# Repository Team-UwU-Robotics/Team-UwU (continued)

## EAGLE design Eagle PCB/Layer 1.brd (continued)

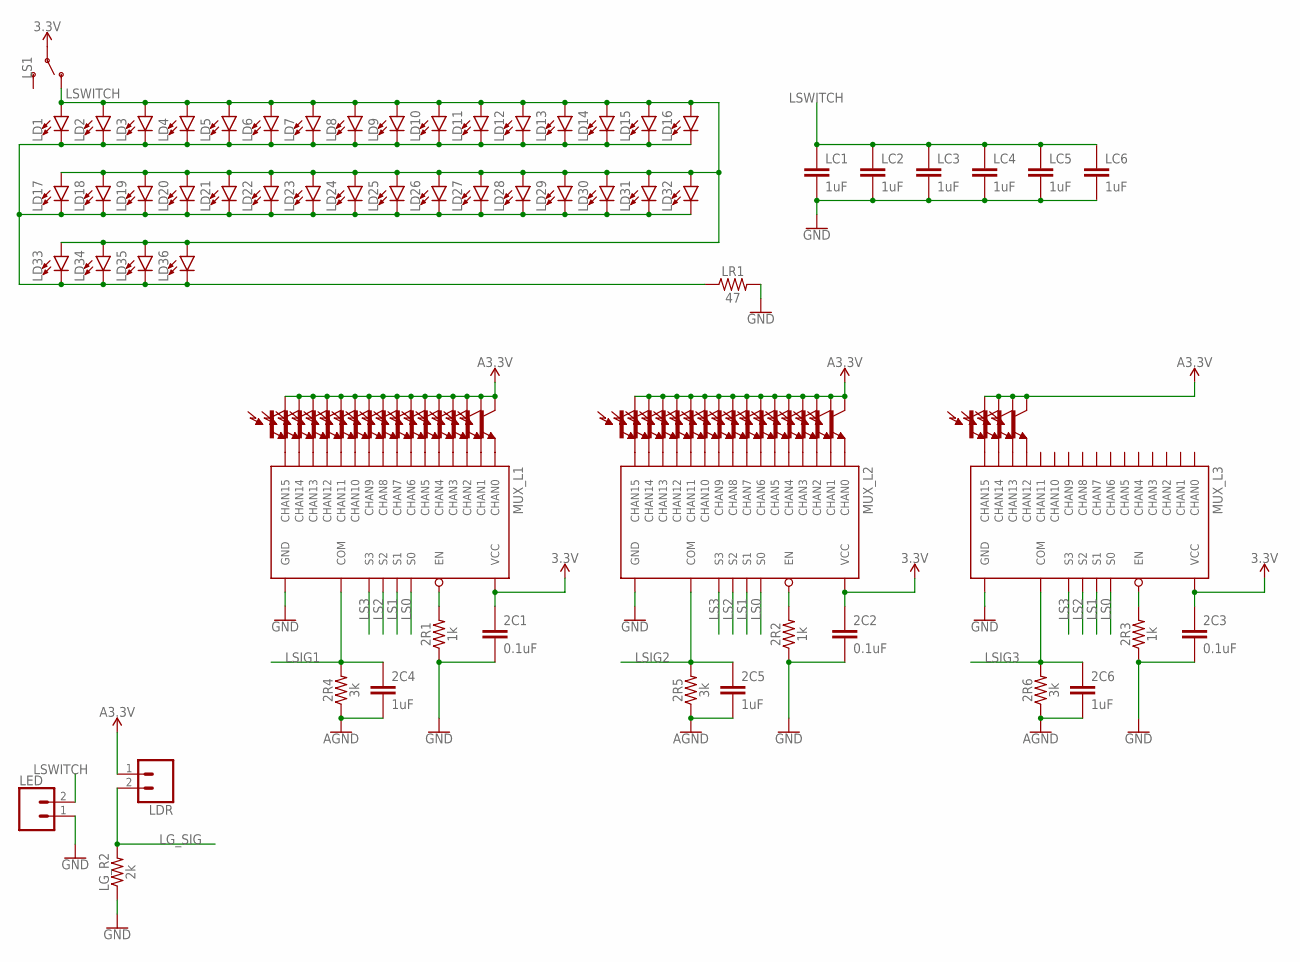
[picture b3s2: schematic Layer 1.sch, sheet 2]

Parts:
2C1, 2C2, 2C3: 0.1uF; C0603
2C4, 2C5, 2C6: 1uF; C0603
2R1, 2R2, 2R3: 1k; R0603
2R4, 2R5, 2R6: 3k; R0603
LC1, LC2, LC3, LC4, LC5, LC6: 1uF; C0603
LD1, LD2, LD3, LD4, LD5, LD6, LD7, LD8, LD9, LD10, LD11, LD12, LD13, LD14, LD15, LD16, LD17, LD18, LD19, LD20, LD21, LD22, LD23, LD24, LD25, LD26, LD27, LD28, LD29, LD30, LD31, LD32, LD33, LD34, LD35, LD36: 3528LED; 3528
LDR: CONN_021X02_NO_SILK; 1X02_NO_SILK
LED: CONN_02POLAR; MOLEX-1X2
LG_R2: 2k; R0603
LR1: 47; R0603
LS1: SWITCH-SPDT-PTH-11.6X4.0MM-LOCK; SWITCH_SPDT_PTH_11.6X4.0MM_LOCK
MUX_L1, MUX_L2, MUX_L3: 74HC4067SSOP-24; SSOP24
Q1, Q2, Q3, Q4, Q5, Q6, Q7, Q8, Q9, Q10, Q11, Q12, Q13, Q14, Q15, Q16, Q17, Q18, Q19, Q20, Q21, Q22, Q23, Q24, Q25, Q26, Q27, Q28, Q29, Q30, Q31, Q32, Q33, Q34, Q35, Q36: LIGHT_SENSORALS; ALS-PT19

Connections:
3.3V: 2C1.1, 2C2.1, 2C3.1, LS1.2, MUX_L1.24 (VCC), MUX_L2.24 (VCC), MUX_L3.24 (VCC); also elsewhere on the board
AGND: 2C4.2, 2C5.2, 2C6.2, 2R4.1, 2R5.1, 2R6.1; also elsewhere on the board
GND: 2C1.2, 2C2.2, 2C3.2, 2R1.1, 2R2.1, 2R3.1, LC1.2, LC2.2, LC3.2, LC4.2, LC5.2, LC6.2, LED.1, LG_R2.1, LR1.2, MUX_L1.12 (GND), MUX_L2.12 (GND), MUX_L3.12 (GND); also elsewhere on the board
LG_SIG: LDR.2, LG_R2.2; also elsewhere on the board
LS0: MUX_L1.10 (S0), MUX_L2.10 (S0), MUX_L3.10 (S0); also elsewhere on the board
LS1: MUX_L1.11 (S1), MUX_L2.11 (S1), MUX_L3.11 (S1); also elsewhere on the board
LS2: MUX_L1.14 (S2), MUX_L2.14 (S2), MUX_L3.14 (S2); also elsewhere on the board
LS3: MUX_L1.13 (S3), MUX_L2.13 (S3), MUX_L3.13 (S3); also elsewhere on the board
LSIG1: 2C4.1, 2R4.2, MUX_L1.1 (COM); also elsewhere on the board
LSIG2: 2C5.1, 2R5.2, MUX_L2.1 (COM); also elsewhere on the board
LSIG3: 2C6.1, 2R6.2, MUX_L3.1 (COM); also elsewhere on the board
LSWITCH: LC1.1, LC2.1, LC3.1, LC4.1, LC5.1, LC6.1, LD1.A, LD2.A, LD3.A, LD4.A, LD5.A, LD6.A, LD7.A, LD8.A, LD9.A, LD10.A, LD11.A, LD12.A, LD13.A, LD14.A, LD15.A, LD16.A, LD17.A, LD18.A, LD19.A, LD20.A, LD21.A, LD22.A, LD23.A, LD24.A, LD25.A, LD26.A, LD27.A, LD28.A, LD29.A, LD30.A, LD31.A, LD32.A, LD33.A, LD34.A, LD35.A, LD36.A, LED.2, LS1.1 (O)
unnamed: 2R1.2, MUX_L1.15 (EN)
unnamed: MUX_L1.16 (CHAN15), Q1.E (E1)
unnamed: MUX_L1.17 (CHAN14), Q2.E (E1)
unnamed: MUX_L1.18 (CHAN13), Q3.E (E1)
unnamed: MUX_L1.19 (CHAN12), Q4.E (E1)
unnamed: MUX_L1.20 (CHAN11), Q5.E (E1)
unnamed: MUX_L1.21 (CHAN10), Q6.E (E1)
unnamed: MUX_L1.22 (CHAN9), Q7.E (E1)
unnamed: MUX_L1.23 (CHAN8), Q8.E (E1)
unnamed: MUX_L1.2 (CHAN7), Q9.E (E1)
unnamed: MUX_L1.3 (CHAN6), Q10.E (E1)
unnamed: MUX_L1.4 (CHAN5), Q11.E (E1)
unnamed: MUX_L1.5 (CHAN4), Q12.E (E1)
unnamed: MUX_L1.6 (CHAN3), Q13.E (E1)
unnamed: MUX_L1.7 (CHAN2), Q14.E (E1)
unnamed: MUX_L1.8 (CHAN1), Q15.E (E1)
unnamed: MUX_L1.9 (CHAN0), Q16.E (E1)
unnamed: LD1.C, LD2.C, LD3.C, LD4.C, LD5.C, LD6.C, LD7.C, LD8.C, LD9.C, LD10.C, LD11.C, LD12.C, LD13.C, LD14.C, LD15.C, LD16.C, LD17.C, LD18.C, LD19.C, LD20.C, LD21.C, LD22.C, LD23.C, LD24.C, LD25.C, LD26.C, LD27.C, LD28.C, LD29.C, LD30.C, LD31.C, LD32.C, LD33.C, LD34.C, LD35.C, LD36.C, LR1.1
unnamed: 2R2.2, MUX_L2.15 (EN)
unnamed: MUX_L2.16 (CHAN15), Q17.E (E1)
unnamed: MUX_L2.17 (CHAN14), Q18.E (E1)
unnamed: MUX_L2.18 (CHAN13), Q19.E (E1)
unnamed: MUX_L2.19 (CHAN12), Q20.E (E1)
unnamed: MUX_L2.20 (CHAN11), Q21.E (E1)
unnamed: MUX_L2.21 (CHAN10), Q22.E (E1)
unnamed: MUX_L2.22 (CHAN9), Q23.E (E1)
unnamed: MUX_L2.23 (CHAN8), Q24.E (E1)
unnamed: MUX_L2.2 (CHAN7), Q25.E (E1)
unnamed: MUX_L2.3 (CHAN6), Q26.E (E1)
unnamed: MUX_L2.4 (CHAN5), Q27.E (E1)
unnamed: MUX_L2.5 (CHAN4), Q28.E (E1)
unnamed: MUX_L2.6 (CHAN3), Q29.E (E1)
unnamed: MUX_L2.7 (CHAN2), Q30.E (E1)
unnamed: MUX_L2.8 (CHAN1), Q31.E (E1)
unnamed: MUX_L2.9 (CHAN0), Q32.E (E1)
unnamed: 2R3.2, MUX_L3.15 (EN)
unnamed: MUX_L3.16 (CHAN15), Q33.E (E1)
unnamed: MUX_L3.17 (CHAN14), Q34.E (E1)
unnamed: MUX_L3.18 (CHAN13), Q35.E (E1)
unnamed: MUX_L3.19 (CHAN12), Q36.E (E1)
VCCA: LDR.1, Q1.C (C1), Q2.C (C1), Q3.C (C1), Q4.C (C1), Q5.C (C1), Q6.C (C1), Q7.C (C1), Q8.C (C1), Q9.C (C1), Q10.C (C1), Q11.C (C1), Q12.C (C1), Q13.C (C1), Q14.C (C1), Q15.C (C1), Q16.C (C1), Q17.C (C1), Q18.C (C1), Q19.C (C1), Q20.C (C1), Q21.C (C1), Q22.C (C1), Q23.C (C1), Q24.C (C1), Q25.C (C1), Q26.C (C1), Q27.C (C1), Q28.C (C1), Q29.C (C1), Q30.C (C1), Q31.C (C1), Q32.C (C1), Q33.C (C1), Q34.C (C1), Q35.C (C1), Q36.C (C1); also elsewhere on the board

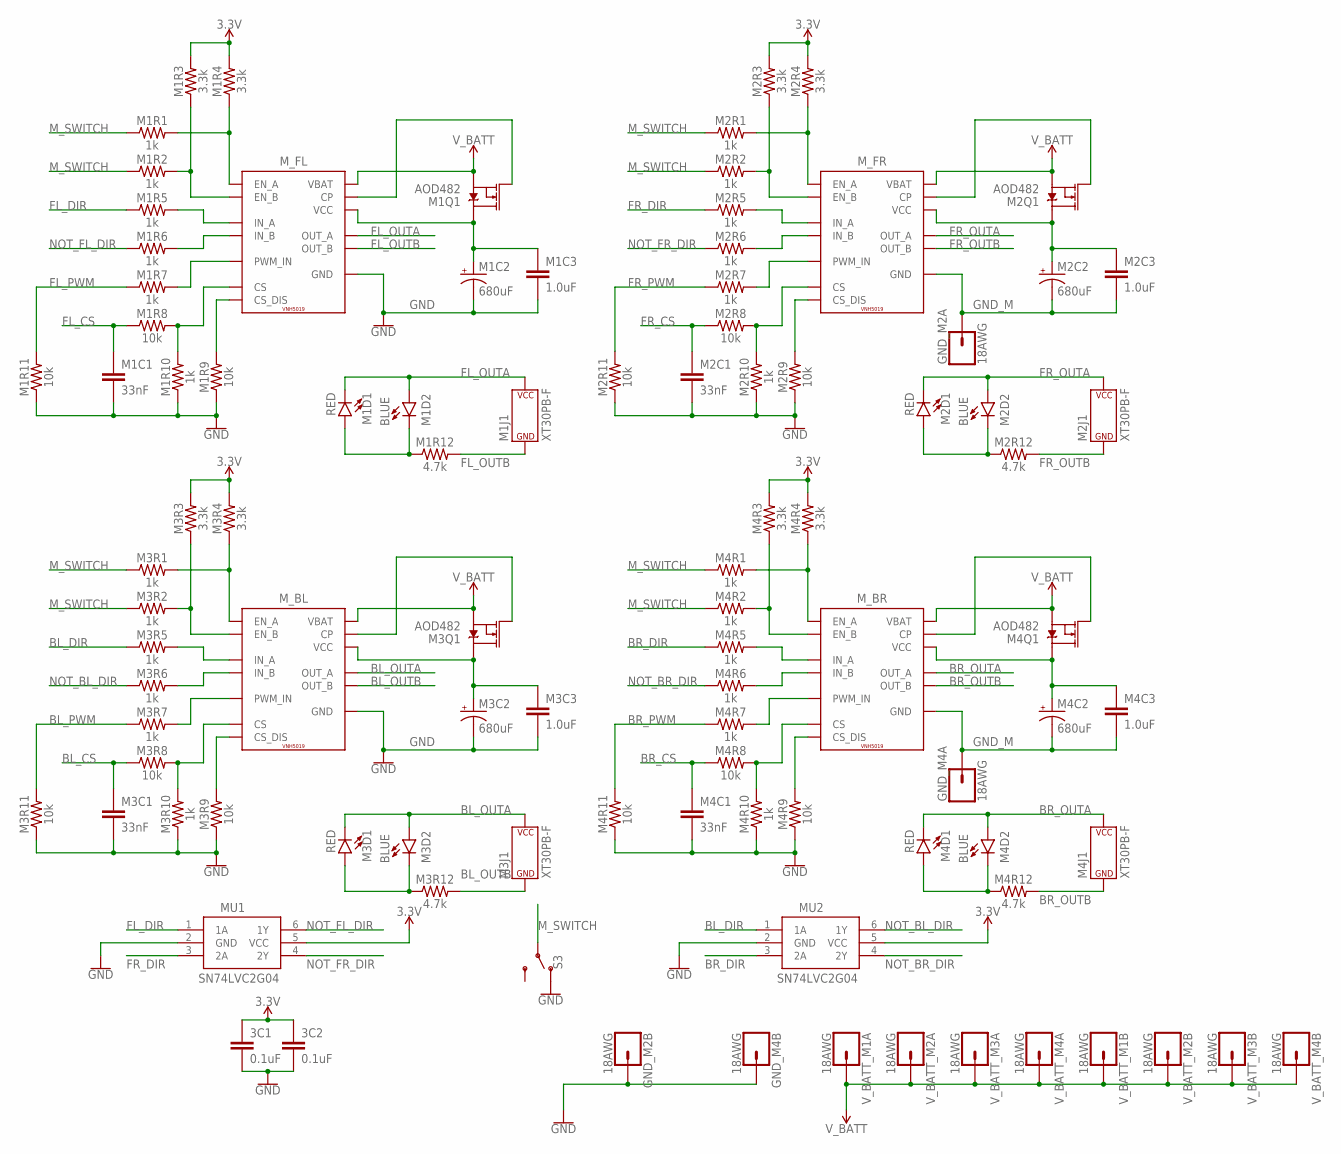
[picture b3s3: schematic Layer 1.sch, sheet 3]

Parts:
3C1, 3C2: 0.1uF; C0603
GND_M2A, GND_M2B, GND_M4A, GND_M4B: 18AWG
M1C1, M2C1, M3C1, M4C1: 33nF; C0603
M1C2, M2C2, M3C2, M4C2: 680uF; 3.5MM_CAP
M1C3, M2C3, M3C3, M4C3: 1.0uF; C0603
M1D1, M2D1, M3D1, M4D1: RED; LED-0603
M1D2, M2D2, M3D2, M4D2: BLUE; LED-0603
M1J1, M2J1, M3J1, M4J1: XT30PB-F
M1Q1, M2Q1, M3Q1, M4Q1: AOD482; DPAK
M1R1, M1R2, M1R5, M1R6, M1R7, M1R10, M2R1, M2R2, M2R5, M2R6, M2R7, M2R10, M3R1, M3R2, M3R5, M3R6, M3R7, M3R10, M4R1, M4R2, M4R5, M4R6, M4R7, M4R10: 1k; R0603
M1R3, M1R4, M2R3, M2R4, M3R3, M3R4, M4R3, M4R4: 3.3k; R0603
M1R8, M1R9, M1R11, M2R8, M2R9, M2R11, M3R8, M3R9, M3R11, M4R8, M4R9, M4R11: 10k; R0603
M1R12, M2R12, M3R12, M4R12: 4.7k; R0603
MU1, MU2: SN74LVC2G04DBVR; SOT23-6
M_BL: VNH5019; POWERSO-30
M_BR: VNH5019; POWERSO-30
M_FL: VNH5019; POWERSO-30
M_FR: VNH5019; POWERSO-30
S3: SWITCH-SPDT-PTH-11.6X4.0MM-LOCK; SWITCH_SPDT_PTH_11.6X4.0MM_LOCK
V_BATT_M1A, V_BATT_M1B, V_BATT_M2A, V_BATT_M2B, V_BATT_M3A, V_BATT_M3B, V_BATT_M4A, V_BATT_M4B: 18AWG

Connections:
3.3V: 3C1.1, 3C2.1, M1R3.2, M1R4.2, M2R3.2, M2R4.2, M3R3.2, M3R4.2, M4R3.2, M4R4.2, MU1.5 (VCC), MU2.5 (VCC); also elsewhere on the board
BL_CS: M3C1.1, M3R8.1; also elsewhere on the board
BL_DIR: M3R5.1, MU2.1 (1A); also elsewhere on the board
BL_OUTA: M3D1.C, M3D2.A, M3J1.+ (P$V+), M_BL.P1 (OUT_A), M_BL.P25 (OUT_A), M_BL.P30 (OUT_A), M_BL.P$1 (OUT_A), M_BL.P$2 (OUT_A), M_BL.P$3 (OUT_A), M_BL.P$4 (OUT_A), M_BL.P$5 (OUT_A), M_BL.P$6 (OUT_A), M_BL.P$7 (OUT_A), M_BL.P$8 (OUT_A), M_BL.P$9 (OUT_A), M_BL.SLUG2 (OUT_A)
BL_OUTB: M3J1.- (P$V-), M3R12.2, M_BL.P15 (OUT_B), M_BL.P16 (OUT_B), M_BL.P21 (OUT_B), M_BL.P$10 (OUT_B), M_BL.P$11 (OUT_B), M_BL.P$12 (OUT_B), M_BL.P$13 (OUT_B), M_BL.P$14 (OUT_B), M_BL.P$15 (OUT_B), M_BL.P$16 (OUT_B), M_BL.P$17 (OUT_B), M_BL.P$18 (OUT_B), M_BL.SLUG3 (OUT_B)
BL_PWM: M3R7.1, M3R11.2; also elsewhere on the board
BR_CS: M4C1.1, M4R8.1; also elsewhere on the board
BR_DIR: M4R5.1, MU2.3 (2A); also elsewhere on the board
BR_OUTA: M4D1.C, M4D2.A, M4J1.+ (P$V+), M_BR.P1 (OUT_A), M_BR.P25 (OUT_A), M_BR.P30 (OUT_A), M_BR.P$1 (OUT_A), M_BR.P$2 (OUT_A), M_BR.P$3 (OUT_A), M_BR.P$4 (OUT_A), M_BR.P$5 (OUT_A), M_BR.P$6 (OUT_A), M_BR.P$7 (OUT_A), M_BR.P$8 (OUT_A), M_BR.P$9 (OUT_A), M_BR.SLUG2 (OUT_A)
BR_OUTB: M4J1.- (P$V-), M4R12.2, M_BR.P15 (OUT_B), M_BR.P16 (OUT_B), M_BR.P21 (OUT_B), M_BR.P$10 (OUT_B), M_BR.P$11 (OUT_B), M_BR.P$12 (OUT_B), M_BR.P$13 (OUT_B), M_BR.P$14 (OUT_B), M_BR.P$15 (OUT_B), M_BR.P$16 (OUT_B), M_BR.P$17 (OUT_B), M_BR.P$18 (OUT_B), M_BR.SLUG3 (OUT_B)
BR_PWM: M4R7.1, M4R11.2; also elsewhere on the board
FL_CS: M1C1.1, M1R8.1; also elsewhere on the board
FL_DIR: M1R5.1, MU1.1 (1A); also elsewhere on the board
FL_OUTA: M1D1.C, M1D2.A, M1J1.+ (P$V+), M_FL.P1 (OUT_A), M_FL.P25 (OUT_A), M_FL.P30 (OUT_A), M_FL.P$1 (OUT_A), M_FL.P$2 (OUT_A), M_FL.P$3 (OUT_A), M_FL.P$4 (OUT_A), M_FL.P$5 (OUT_A), M_FL.P$6 (OUT_A), M_FL.P$7 (OUT_A), M_FL.P$8 (OUT_A), M_FL.P$9 (OUT_A), M_FL.SLUG2 (OUT_A)
FL_OUTB: M1J1.- (P$V-), M1R12.2, M_FL.P15 (OUT_B), M_FL.P16 (OUT_B), M_FL.P21 (OUT_B), M_FL.P$10 (OUT_B), M_FL.P$11 (OUT_B), M_FL.P$12 (OUT_B), M_FL.P$13 (OUT_B), M_FL.P$14 (OUT_B), M_FL.P$15 (OUT_B), M_FL.P$16 (OUT_B), M_FL.P$17 (OUT_B), M_FL.P$18 (OUT_B), M_FL.SLUG3 (OUT_B)
FL_PWM: M1R7.1, M1R11.2; also elsewhere on the board
FR_CS: M2C1.1, M2R8.1; also elsewhere on the board
FR_DIR: M2R5.1, MU1.3 (2A); also elsewhere on the board
FR_OUTA: M2D1.C, M2D2.A, M2J1.+ (P$V+), M_FR.P1 (OUT_A), M_FR.P25 (OUT_A), M_FR.P30 (OUT_A), M_FR.P$1 (OUT_A), M_FR.P$2 (OUT_A), M_FR.P$3 (OUT_A), M_FR.P$4 (OUT_A), M_FR.P$5 (OUT_A), M_FR.P$6 (OUT_A), M_FR.P$7 (OUT_A), M_FR.P$8 (OUT_A), M_FR.P$9 (OUT_A), M_FR.SLUG2 (OUT_A)
FR_OUTB: M2J1.- (P$V-), M2R12.2, M_FR.P15 (OUT_B), M_FR.P16 (OUT_B), M_FR.P21 (OUT_B), M_FR.P$10 (OUT_B), M_FR.P$11 (OUT_B), M_FR.P$12 (OUT_B), M_FR.P$13 (OUT_B), M_FR.P$14 (OUT_B), M_FR.P$15 (OUT_B), M_FR.P$16 (OUT_B), M_FR.P$17 (OUT_B), M_FR.P$18 (OUT_B), M_FR.SLUG3 (OUT_B)
FR_PWM: M2R7.1, M2R11.2; also elsewhere on the board
GND: 3C1.2, 3C2.2, GND_M2B.P$1, GND_M4B.P$1, M1C1.2, M1C2.2 (-), M1C3.2, M1R9.1, M1R10.1, M1R11.1, M2C1.2, M2R9.1, M2R10.1, M2R11.1, M3C1.2, M3C2.2 (-), M3C3.2, M3R9.1, M3R10.1, M3R11.1, M4C1.2, M4R9.1, M4R10.1, M4R11.1, MU1.2 (GND), MU2.2 (GND), M_BL.P18 (GND), M_BL.P19 (GND), M_BL.P20 (GND), M_BL.P26 (GND), M_BL.P27 (GND), M_BL.P28 (GND), M_FL.P18 (GND), M_FL.P19 (GND), M_FL.P20 (GND), M_FL.P26 (GND), M_FL.P27 (GND), M_FL.P28 (GND), S3.1 (O); also elsewhere on the board
GND_M: GND_M2A.P$1, GND_M4A.P$1, M2C2.2 (-), M2C3.2, M4C2.2 (-), M4C3.2, M_BR.P18 (GND), M_BR.P19 (GND), M_BR.P20 (GND), M_BR.P26 (GND), M_BR.P27 (GND), M_BR.P28 (GND), M_FR.P18 (GND), M_FR.P19 (GND), M_FR.P20 (GND), M_FR.P26 (GND), M_FR.P27 (GND), M_FR.P28 (GND)
M_SWITCH: M1R1.1, M1R2.1, M2R1.1, M2R2.1, M3R1.1, M3R2.1, M4R1.1, M4R2.1, S3.2
unnamed: M1R1.2, M1R4.1, M_FL.P5 (EN_A)
unnamed: M1R2.2, M1R3.1, M_FL.P9 (EN_B)
unnamed: M1R5.2, M_FL.P4 (IN_A)
unnamed: M1R6.2, M_FL.P10 (IN_B)
unnamed: M1R7.2, M_FL.P7 (PWM_IN)
unnamed: M1R8.2, M1R10.2, M_FL.P8 (CS)
unnamed: M1R9.2, M_FL.P6 (CS_DIS)
unnamed: M1C2.1 (+), M1C3.1, M1Q1.4 (D), M_FL.P3 (VCC), M_FL.P13 (VCC), M_FL.P23 (VCC), M_FL.P$19 (VCC), M_FL.P$20 (VCC), M_FL.P$21 (VCC), M_FL.P$22 (VCC), M_FL.P$23 (VCC), M_FL.P$24 (VCC), M_FL.P$25 (VCC), M_FL.P$26 (VCC), M_FL.P$27 (VCC), M_FL.P$28 (VCC), M_FL.SLUG1 (VCC)
unnamed: M1Q1.1 (G), M_FL.P11 (CP)
unnamed: M2R2.2, M2R3.1, M_FR.P9 (EN_B)
unnamed: M1D1.A, M1D2.C, M1R12.1
unnamed: M2R1.2, M2R4.1, M_FR.P5 (EN_A)
unnamed: M2R6.2, M_FR.P10 (IN_B)
unnamed: M2R5.2, M_FR.P4 (IN_A)
unnamed: M2R7.2, M_FR.P7 (PWM_IN)
unnamed: M2R8.2, M2R10.2, M_FR.P8 (CS)
unnamed: M2R9.2, M_FR.P6 (CS_DIS)
unnamed: M2C2.1 (+), M2C3.1, M2Q1.4 (D), M_FR.P3 (VCC), M_FR.P13 (VCC), M_FR.P23 (VCC), M_FR.P$19 (VCC), M_FR.P$20 (VCC), M_FR.P$21 (VCC), M_FR.P$22 (VCC), M_FR.P$23 (VCC), M_FR.P$24 (VCC), M_FR.P$25 (VCC), M_FR.P$26 (VCC), M_FR.P$27 (VCC), M_FR.P$28 (VCC), M_FR.SLUG1 (VCC)
unnamed: M2Q1.1 (G), M_FR.P11 (CP)
unnamed: M3R2.2, M3R3.1, M_BL.P9 (EN_B)
unnamed: M2D1.A, M2D2.C, M2R12.1
unnamed: M3R1.2, M3R4.1, M_BL.P5 (EN_A)
unnamed: M3R6.2, M_BL.P10 (IN_B)
unnamed: M3R5.2, M_BL.P4 (IN_A)
unnamed: M3R7.2, M_BL.P7 (PWM_IN)
unnamed: M3R8.2, M3R10.2, M_BL.P8 (CS)
unnamed: M3R9.2, M_BL.P6 (CS_DIS)
unnamed: M3C2.1 (+), M3C3.1, M3Q1.4 (D), M_BL.P3 (VCC), M_BL.P13 (VCC), M_BL.P23 (VCC), M_BL.P$19 (VCC), M_BL.P$20 (VCC), M_BL.P$21 (VCC), M_BL.P$22 (VCC), M_BL.P$23 (VCC), M_BL.P$24 (VCC), M_BL.P$25 (VCC), M_BL.P$26 (VCC), M_BL.P$27 (VCC), M_BL.P$28 (VCC), M_BL.SLUG1 (VCC)
unnamed: M3Q1.1 (G), M_BL.P11 (CP)
unnamed: M4R2.2, M4R3.1, M_BR.P9 (EN_B)
unnamed: M4R1.2, M4R4.1, M_BR.P5 (EN_A)
unnamed: M4R6.2, M_BR.P10 (IN_B)
unnamed: M4R5.2, M_BR.P4 (IN_A)
unnamed: M4R7.2, M_BR.P7 (PWM_IN)
unnamed: M3D1.A, M3D2.C, M3R12.1
unnamed: M4R8.2, M4R10.2, M_BR.P8 (CS)
unnamed: M4R9.2, M_BR.P6 (CS_DIS)
unnamed: M4C2.1 (+), M4C3.1, M4Q1.4 (D), M_BR.P3 (VCC), M_BR.P13 (VCC), M_BR.P23 (VCC), M_BR.P$19 (VCC), M_BR.P$20 (VCC), M_BR.P$21 (VCC), M_BR.P$22 (VCC), M_BR.P$23 (VCC), M_BR.P$24 (VCC), M_BR.P$25 (VCC), M_BR.P$26 (VCC), M_BR.P$27 (VCC), M_BR.P$28 (VCC), M_BR.SLUG1 (VCC)
unnamed: M4Q1.1 (G), M_BR.P11 (CP)
unnamed: M4D1.A, M4D2.C, M4R12.1
NOT_BL_DIR: M3R6.1, MU2.6 (1Y)
NOT_BR_DIR: M4R6.1, MU2.4 (2Y)
NOT_FL_DIR: M1R6.1, MU1.6 (1Y)
NOT_FR_DIR: M2R6.1, MU1.4 (2Y)
V_BATT: M1Q1.3 (S), M2Q1.3 (S), M3Q1.3 (S), M4Q1.3 (S), M_BL.P12 (VBAT), M_BR.P12 (VBAT), M_FL.P12 (VBAT), M_FR.P12 (VBAT), V_BATT_M1A.P$1, V_BATT_M1B.P$1, V_BATT_M2A.P$1, V_BATT_M2B.P$1, V_BATT_M3A.P$1, V_BATT_M3B.P$1, V_BATT_M4A.P$1, V_BATT_M4B.P$1; also elsewhere on the board

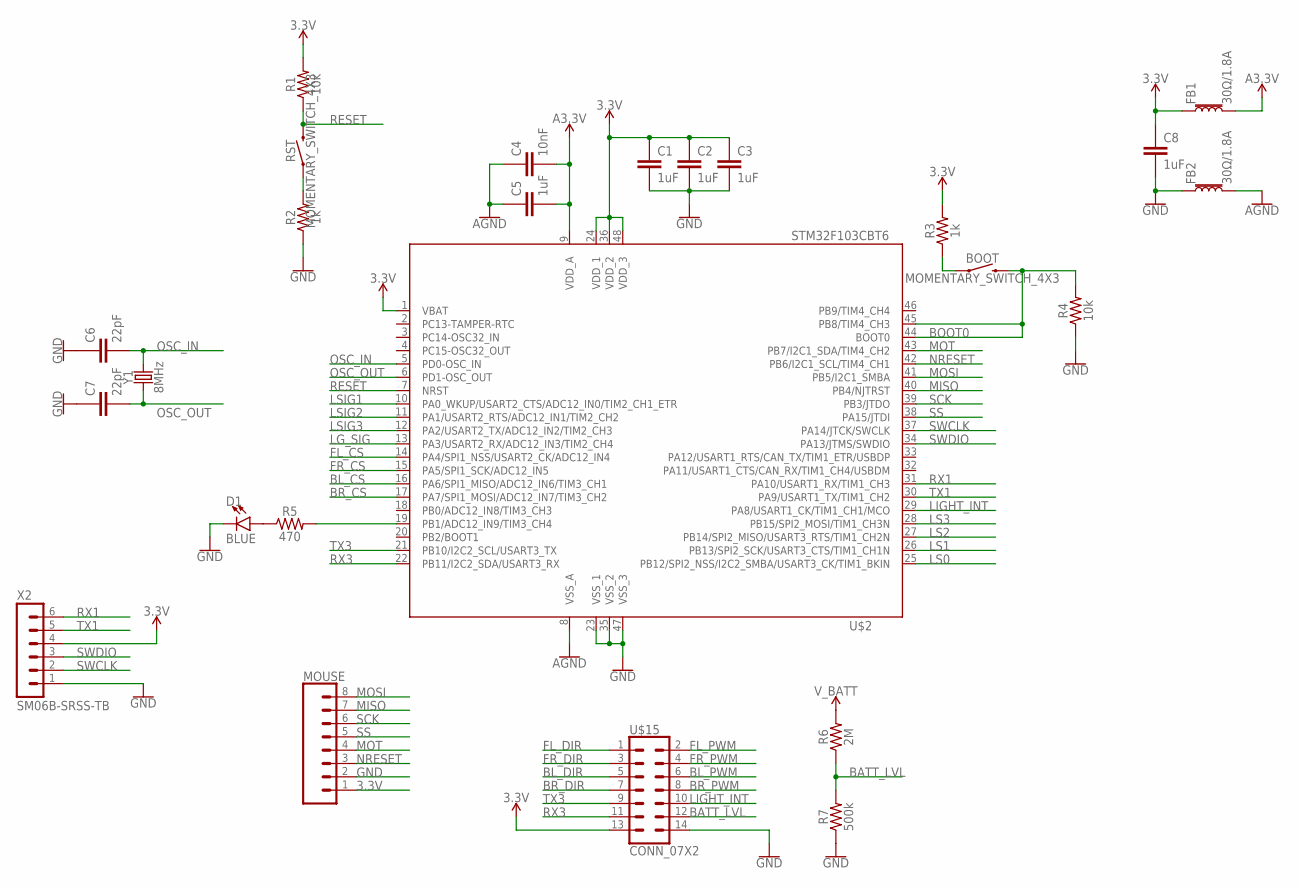
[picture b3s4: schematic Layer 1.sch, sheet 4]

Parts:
BOOT: MOMENTARY_SWITCH_4X3
C1, C2, C3, C5, C8: 1uF; C0603
C4: 10nF; C0603
C6, C7: 22pF; C0603
D1: BLUE; LED-0603
FB1, FB2: 30Ω/1.8A; 0603
MOUSE: CONN_08LOCK; 1X08_LOCK
R1, R4: 10k; R0603
R2, R3: 1k; R0603
R5: 470; R0603
R6: 2M; R0603
R7: 500k; R0603
RST: MOMENTARY_SWITCH_4X3
U$2: STM32F103CBT6; LQFP48
U$15: CONN_07X2; 2X7
X2: SM06B-SRSS-TB
Y1: 8MHz; CRYSTAL-SMD-5X3.2-2PAD

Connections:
3.3V: C1.1, C2.1, C3.1, C8.1, FB1.1, MOUSE.1, R1.2, R3.2, U$2.1 (VBAT), U$2.24 (VDD_1), U$2.36 (VDD_2), U$2.48 (VDD_3), U$15.13, X2.4; also elsewhere on the board
AGND: C4.1, C5.1, FB2.2, U$2.8 (VSS_A); also elsewhere on the board
BATT_LVL: R6.1, R7.2, U$15.12
BL_CS: U$2.16 (PA6/SPI1_MISO/ADC12_IN6/TIM3_CH1); also elsewhere on the board
BL_DIR: U$15.5; also elsewhere on the board
BL_PWM: U$15.6; also elsewhere on the board
BOOT0: BOOT.P$2 (2), R4.2, U$2.44 (BOOT0), U$2.45 (PB8/TIM4_CH3)
BR_CS: U$2.17 (PA7/SPI1_MOSI/ADC12_IN7/TIM3_CH2); also elsewhere on the board
BR_DIR: U$15.7; also elsewhere on the board
BR_PWM: U$15.8; also elsewhere on the board
FL_CS: U$2.14 (PA4/SPI1_NSS/USART2_CK/ADC12_IN4); also elsewhere on the board
FL_DIR: U$15.1; also elsewhere on the board
FL_PWM: U$15.2; also elsewhere on the board
FR_CS: U$2.15 (PA5/SPI1_SCK/ADC12_IN5); also elsewhere on the board
FR_DIR: U$15.3; also elsewhere on the board
FR_PWM: U$15.4; also elsewhere on the board
GND: C1.2, C2.2, C3.2, C6.1, C7.1, C8.2, D1.C, FB2.1, MOUSE.2, R2.1, R4.1, R7.1, U$2.23 (VSS_1), U$2.35 (VSS_2), U$2.47 (VSS_3), U$15.14, X2.1; also elsewhere on the board
LG_SIG: U$2.13 (PA3/USART2_RX/ADC12_IN3/TIM2_CH4); also elsewhere on the board
LIGHT_INT: U$2.29 (PA8/USART1_CK/TIM1_CH1/MCO), U$15.10
LS0: U$2.25 (PB12/SPI2_NSS/I2C2_SMBA/USART3_CK/TIM1_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); also elsewhere on the board
LS1: U$2.26 (PB13/SPI2_SCK/USART3_CTS/TIM1_CH1N); also elsewhere on the board
LS2: U$2.27 (PB14/SPI2_MISO/USART3_RTS/TIM1_CH2N); also elsewhere on the board
LS3: U$2.28 (PB15/SPI2_MOSI/TIM1_CH3N); also elsewhere on the board
LSIG1: U$2.10 (PA0_WKUP/USART2_CTS/ADC12_IN0/TIM2_CH1_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); also elsewhere on the board
LSIG2: U$2.11 (PA1/USART2_RTS/ADC12_IN1/TIM2_CH2); also elsewhere on the board
LSIG3: U$2.12 (PA2/USART2_TX/ADC12_IN2/TIM2_CH3); also elsewhere on the board
MISO: MOUSE.7, U$2.40 (PB4/NJTRST)
MOSI: MOUSE.8, U$2.41 (PB5/I2C1_SMBA)
MOT: MOUSE.4, U$2.43 (PB7/I2C1_SDA/TIM4_CH2)
unnamed: R2.2, RST.P$1 (1)
unnamed: BOOT.P$1 (1), R3.1
unnamed: R5.2, U$2.19 (PB1/ADC12_IN9/TIM3_CH4)
unnamed: D1.A, R5.1
NRESET: MOUSE.3, U$2.42 (PB6/I2C1_SCL/TIM4_CH1)
OSC_IN: C6.2, U$2.5 (PD0-OSC_IN), Y1.P$2 (2)
OSC_OUT: C7.2, U$2.6 (PD1-OSC_OUT), Y1.P$1 (1)
RESET: R1.1, RST.P$2 (2), U$2.7 (NRST)
RX1: U$2.31 (PA10/USART1_RX/TIM1_CH3), X2.6
RX3: U$2.22 (PB11/I2C2_SDA/USART3_RX), U$15.11
SCK: MOUSE.6, U$2.39 (PB3/JTDO)
SS: MOUSE.5, U$2.38 (PA15/JTDI)
SWCLK: U$2.37 (PA14/JTCK/SWCLK), X2.2
SWDIO: U$2.34 (PA13/JTMS/SWDIO), X2.3
TX1: U$2.30 (PA9/USART1_TX/TIM1_CH2), X2.5
TX3: U$2.21 (PB10/I2C2_SCL/USART3_TX), U$15.9
VCCA: C4.2, C5.2, FB1.2, U$2.9 (VDD_A); also elsewhere on the board
V_BATT: R6.2; also elsewhere on the board

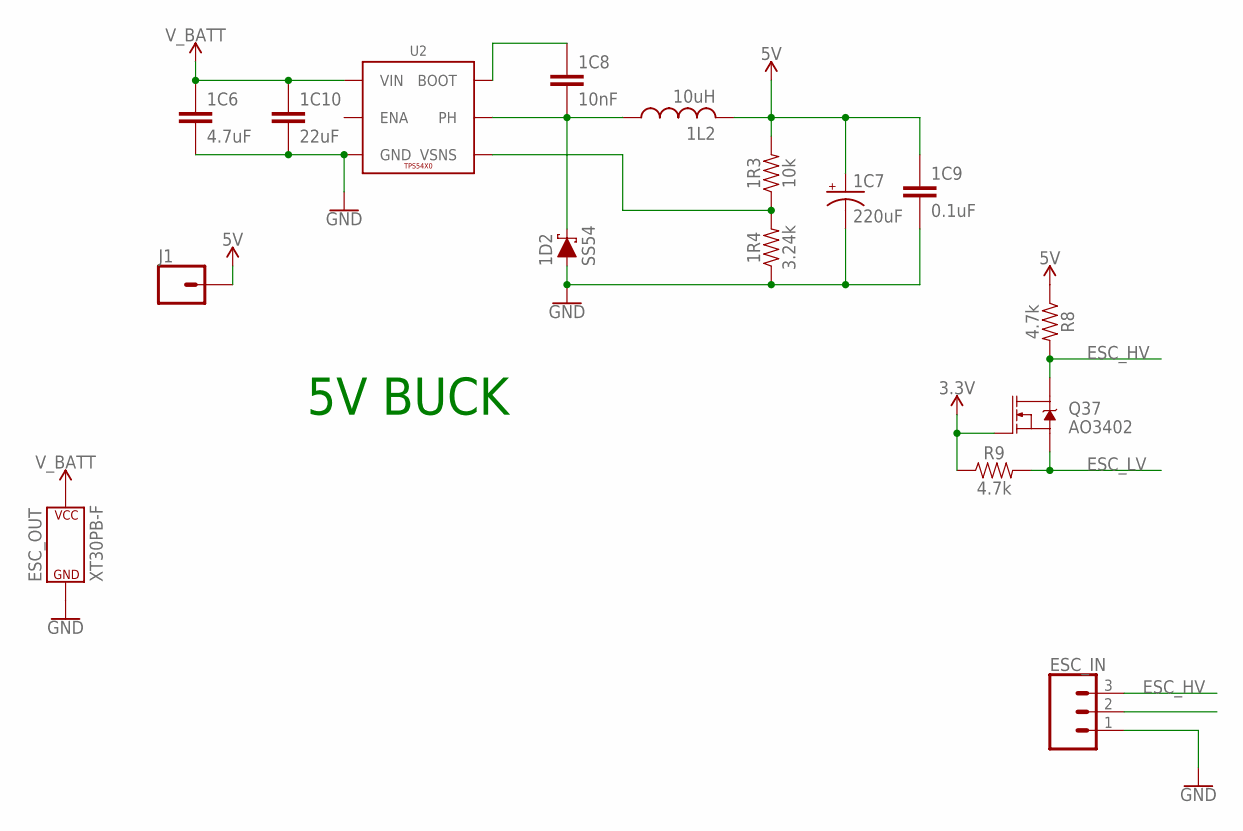
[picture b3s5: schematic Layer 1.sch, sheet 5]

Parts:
1C6: 4.7uF; C0603
1C7: 220uF; EIA7343
1C8: 10nF; C0603
1C9: 0.1uF; C0603
1C10: 22uF; C1210
1D2: SS54; SMA-DIODE
1L2: 10uH; SWPA8040
1R3: 10k; R0603
1R4: 3.24k; R0603
ESC_IN: CONN_03LOCK; 1X03_LOCK
ESC_OUT: XT30PB-F
J1: CONN_01; 1X01
Q37: AO3402; SOT23-3
R8, R9: 4.7k; R0603
U2: TPS54X0; POWERPAD-SOIC-8

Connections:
3.3V1: Q37.1 (G), R9.1
ESC_HV: ESC_IN.3, Q37.3 (D), R8.2
GND: 1C6.2, 1C7.C (-), 1C9.2, 1C10.2, 1D2.A, 1R4.1, ESC_IN.1, ESC_OUT.- (P$V-), U2.6 (GND), U2.9 (GND), U2.P$1 (GND), U2.P$2 (GND), U2.P$3 (GND), U2.P$4 (GND), U2.P$5 (GND), U2.P$6 (GND); also elsewhere on the board
unnamed: 1C8.2, 1D2.C, 1L2.P1 (1), U2.8 (PH)
unnamed: 1R3.1, 1R4.2, U2.4 (VSNS)
unnamed: 1C8.1, U2.1 (BOOT)
V_BATT: 1C6.1, 1C10.1, ESC_OUT.+ (P$V+), U2.7 (VIN); also elsewhere on the board

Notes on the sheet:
5V BUCK

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
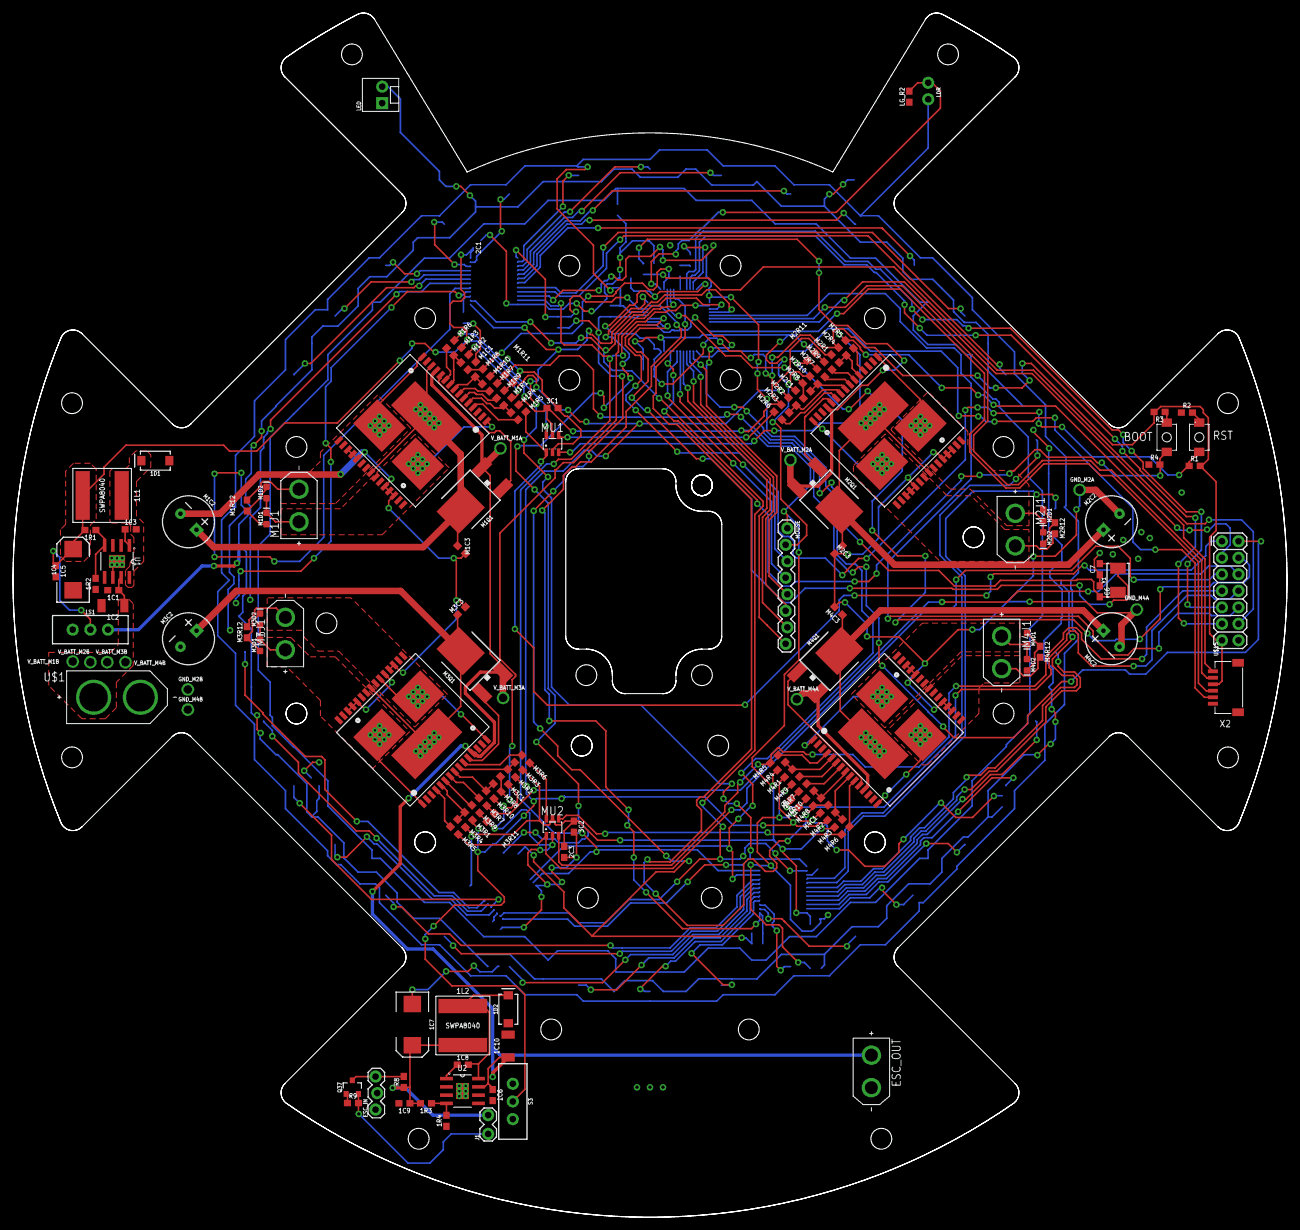
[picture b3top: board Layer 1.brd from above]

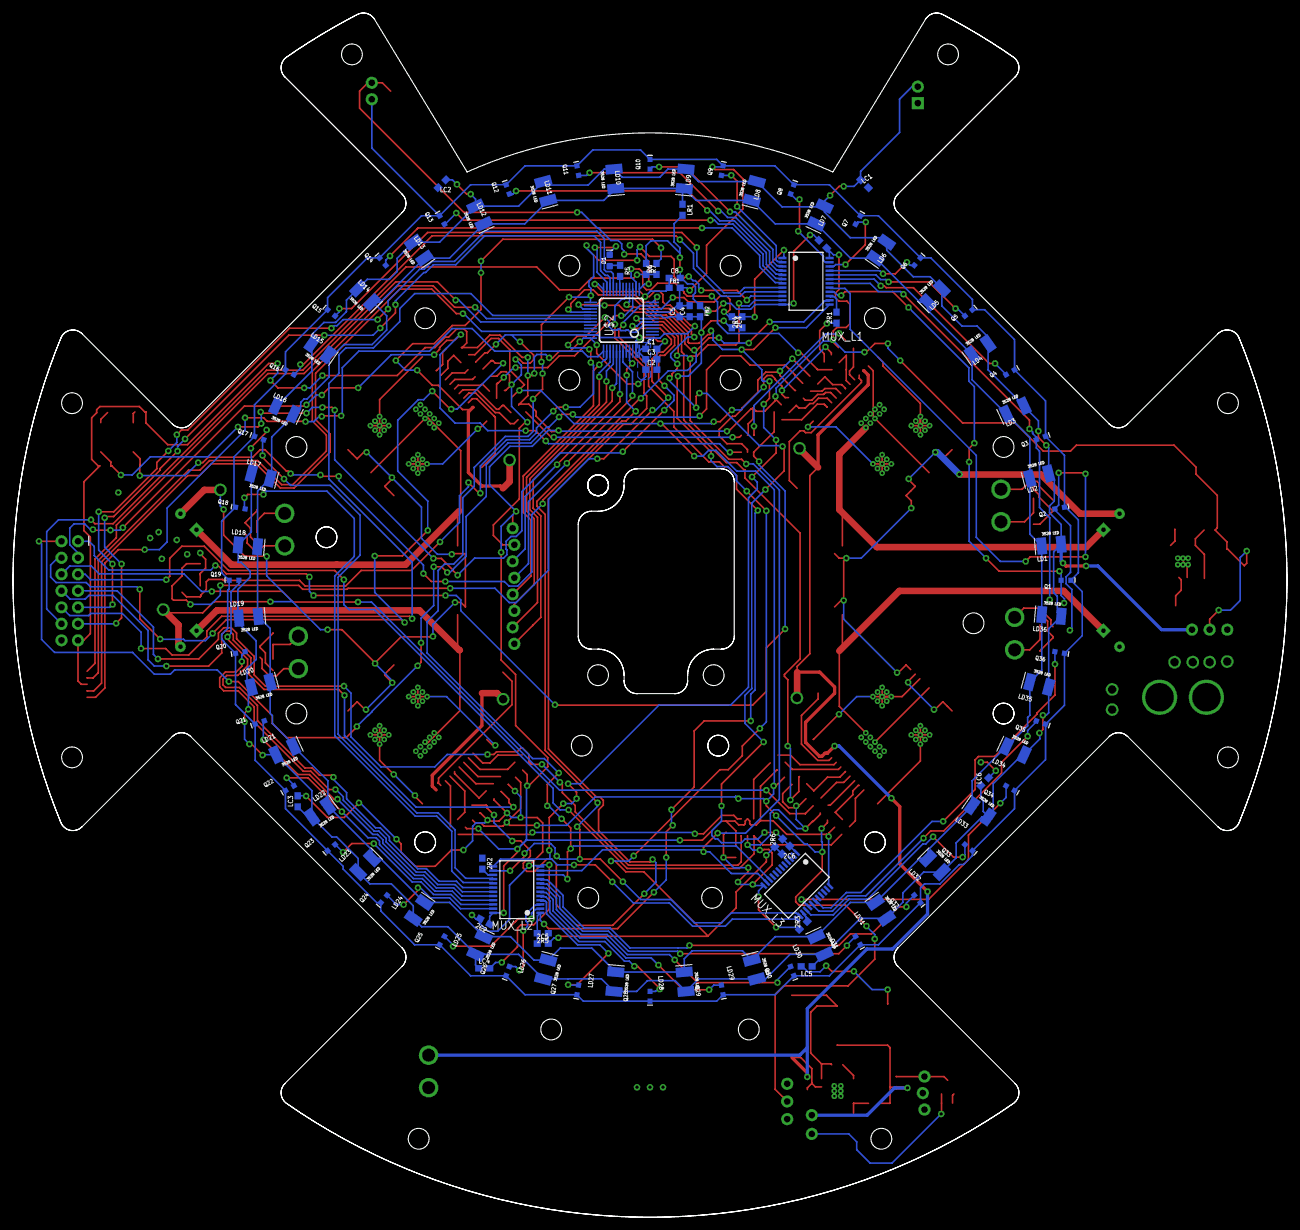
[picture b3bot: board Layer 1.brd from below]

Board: 2 copper layers, 196.0 x 185.3 mm, 247 parts (106 on the bottom side), 152 nets.

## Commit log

2021-01-15 ir sensor layer added (layer 3)
2021-01-15 Mirror-Layer-Added
2021-01-15 Cleaning-Up
2021-01-15 Eagle-PCB
2021-01-16 Layer3-IRSensors
2021-02-05 Layer 1
2021-02-13 Done
2021-02-19 Shit
2021-02-19 Retard
2021-02-19 Fuck you
2021-02-24 Hello
2021-02-26 macOS
2021-02-28 Final
2021-02-28 Fucking Done
2021-03-01 Layer 1 ESC fix
2021-03-01 Revert "Layer 1 ESC fix"
    This reverts commit 0f488ec0a57c37762cb3c7e9928ac58a828ee823.
2021-03-01 Part-List
2021-03-01 Include the part links
